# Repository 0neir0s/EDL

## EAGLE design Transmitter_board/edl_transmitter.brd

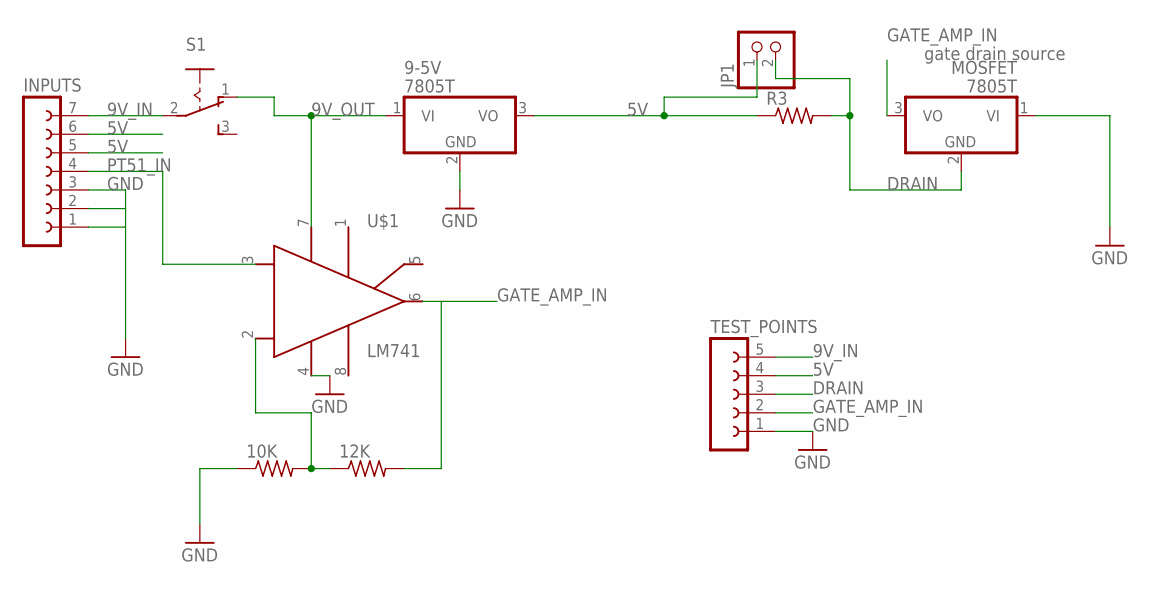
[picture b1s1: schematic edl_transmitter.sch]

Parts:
9-5V: 7805T; TO220H
10K, 12K: R-US_0207/10; 0207/10
INPUTS: FE07-1; FE07
JP1: PINHD-1X2; 1X02
MOSFET: 7805T; TO220H
R3: R-US_0207/10; 0207/10
S1: 255SB
TEST_POINTS: FE05-1
U$1: OPAMP-741-DIP

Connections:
5V: 9-5V.3 (VO), INPUTS.5, INPUTS.6, JP1.1, R3.1, TEST_POINTS.4
9V_IN: INPUTS.7, S1.2, TEST_POINTS.5
9V_OUT: 9-5V.1 (VI), S1.1 (O), U$1.7
DRAIN: JP1.2, MOSFET.2 (GND), R3.2, TEST_POINTS.3
GATE_AMP_IN: 12K.2, MOSFET.3 (VO), TEST_POINTS.2, U$1.6
GND: 9-5V.2 (GND), 10K.1, INPUTS.1, INPUTS.2, INPUTS.3, MOSFET.1 (VI), TEST_POINTS.1, U$1.4
unnamed: 10K.2, 12K.1, U$1.2
PT51_IN: INPUTS.4, U$1.3

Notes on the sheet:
gate drain source

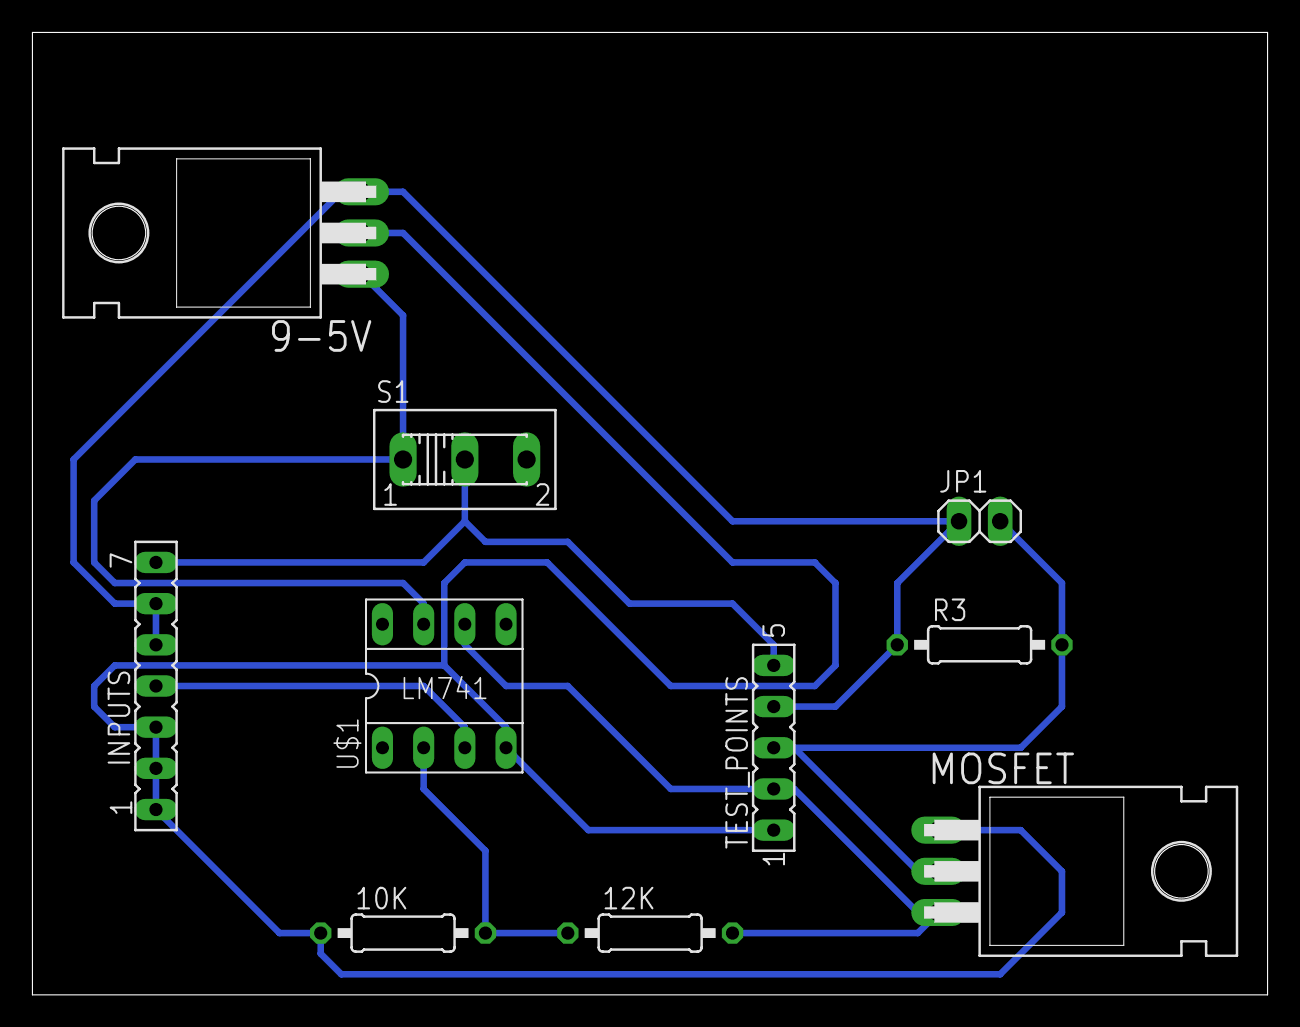
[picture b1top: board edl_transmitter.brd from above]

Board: 2 copper layers, 76.2 x 59.4 mm, 10 parts (0 on the bottom side), 8 nets.

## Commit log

2017-02-16 Continuously sending code
2017-02-16 Evaluation-1
2017-02-26 Added book for tiva C
2017-03-07 Board added
2017-03-09 2nd evaluation

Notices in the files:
parts and their libraries:
SparkFun-Aesthetics: Licensing: Creative Commons ShareAlike 4.0 International - https://creativecommons.org/licenses/by-sa/4.0
